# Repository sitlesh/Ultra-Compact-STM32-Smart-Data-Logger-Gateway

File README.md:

# Custom Embedded Controller Board with Micro SD Storage

A professionally designed, compact **2-layer printed circuit board (PCB)** developed using **KiCad 8.0**. This hardware platform is engineered for standalone embedded applications requiring localized data logging, high-precision timing, and robust power delivery.

---

## 📸 Hardware Showcase

### 🏷️ 3D Render Preview

### 🗺️ Board Layout (Top & Bottom View)
| Top Copper Layer (F.Cu) | Bottom Copper Layer (B.Cu) |
| :---: | :---: |
|  |  |

---

## 🚀 Key Hardware Features

* **Micro SD Card Slot (J4):** Wired via high-speed SPI interface. Features localized decoupling, direct short-return paths to ground, and integrated mechanical shield grounding (`SH GND`) to suppress ESD and EMI.
* **Dual-Clock Architecture:** * **High-Speed Crystal (Y1 - 8MHz):** Provides a stable external clock source for the primary microcontroller core, stabilized by 20pF loading capacitors.
  * **Low-Speed RTC Crystal (Y2 - 32.768kHz):** Dedicated ultra-low-power crystal with 10pF loading capacitors for precise time-stamping.
* **Power Management:** Heavy-duty 2-position screw terminal (`J1`) for power input, protected by a robust on-board Schottky/Rectifier Diode (`D1`) for reverse polarity protection.
* **Signal Integrity:** Utilizes duplicated, stitched copper zones (`GND`) across both layers to maximize thermal dissipation, lower loop inductance, and suppress high-frequency noise.

---

## 📁 Repository Directory & File Descriptions

This repository contains all the native design assets and manufacturing files required to replicate or modify this project.

### 🛠️ Source Design Files (KiCad 8.0)
* **[`Ultra-Compact STM32 Smart Data Logger & Gateway.kicad_pro`](./Ultra-Compact%20STM32%20Smart%20Data%20Logger%20%26%20Gateway.kicad_pro)** : The master KiCad project file that links the schematic and PCB layout configurations together.
* **[`Ultra-Compact STM32 Smart Data Logger & Gateway.kicad_sch`](./Ultra-Compact%20STM32%20Smart%20Data%20Logger%20%26%20Gateway.kicad_sch)** : The complete schematic capture. Contains the logical circuit connections, component symbols, and electrical nets.
* **[`Ultra-Compact STM32 Smart Data Logger & Gateway.kicad_pcb`](./Ultra-Compact%20STM32%20Smart%20Data%20Logger%20%26%20Gateway.kicad_pcb)** : The physical 2-layer board layout, trace routing, component footprints, and copper ground planes.
* **[`gitignore.txt`](./gitignore.txt)** : Configured to exclude local KiCad auto-saves and temporary backup files to keep the repository clean.

### 📦 Manufacturing Files
* **[`Download Pre-packaged Gerbers ZIP (Gerbers.zip)`](./Gerbers.zip)** : Contains the combined ZIP archive. Click this link and hit the **Download** button on the next page to get all production-ready Gerber and Drill files for direct manufacturing.

---

## ⚙️ Fabrication Specifications

| Parameter | Specification |
| :--- | :--- |
| **Material Type** | FR-4 Standard |
| **Layer Count** | 2 Layers |
| **Board Thickness** | 1.6 mm |
| **Copper Weight** | 1 oz (35μm) outer layers |
| **Surface Finish** | HASL (with lead) or ENIG |
| **Solder Mask** | User Preference (Green/Blue/Black) |
| **Silkscreen** | White (High contrast) |

---

## 📝 License
This hardware design is open-source. Feel free to clone, modify, and build upon it for your own custom applications.

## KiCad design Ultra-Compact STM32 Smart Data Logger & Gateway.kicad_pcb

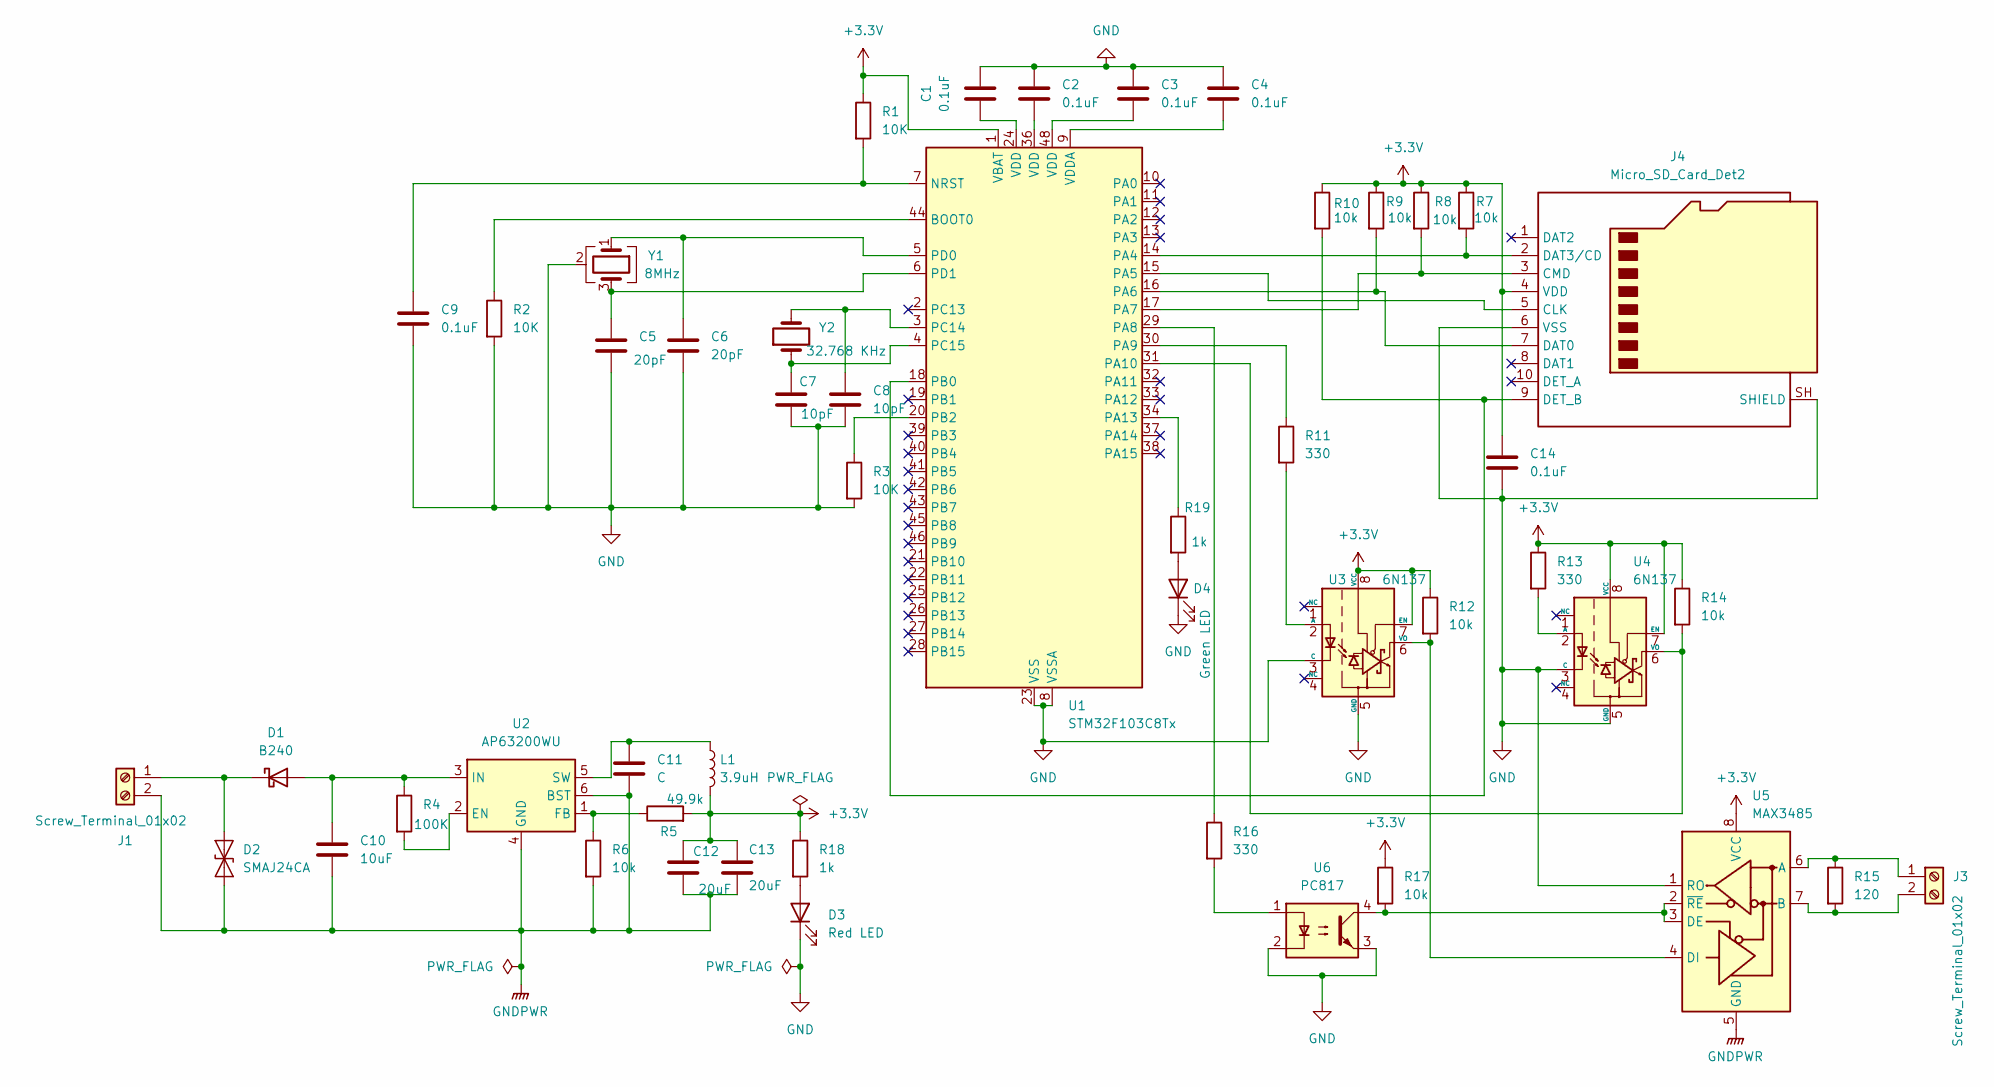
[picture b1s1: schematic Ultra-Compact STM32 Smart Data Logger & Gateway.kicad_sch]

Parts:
C1, C2, C3, C4, C9, C14: 0.1uF; C_0603_1608Metric
C5, C6: 20pF; C_0603_1608Metric
C7, C8: 10pF; C_0603_1608Metric
C10: 10uF; C_0603_1608Metric
C11: C; C_0603_1608Metric
C12, C13: 20uF; C_0603_1608Metric
D1: B240; D_SMB
D2: SMAJ24CA; D_SMA
D3: Red LED; LED_0805_2012Metric
D4: Green LED; LED_0805_2012Metric
J1, J3: Screw_Terminal_01x02; TerminalBlock_Phoenix_MKDS-1,5-2-5.08_1x02_P5.08mm_Horizont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
J4: Micro_SD_Card_Det2; microSD_HC_Molex_104031-0811
L1: 3.9uH; L_6.3x6.3_H3
R1, R2, R3: 10K; R_0805_2012Metric
R4: 100K; R_0805_2012Metric
R5: 49.9k; R_0805_2012Metric
R6, R7, R8, R9, R10, R12, R14, R17: 10k; R_0805_2012Metric
R11, R13, R16: 330; R_0805_2012Metric
R15: 120; R_0805_2012Metric
R18, R19: 1k; R_0805_2012Metric
U1: STM32F103C8Tx; LQFP-48_7x7mm_P0.5mm
U2: AP63200WU; TSOT-23-6
U3, U4: 6N137; SMDIP-8_W7.62mm
U5: MAX3485; SOIC-8_3.9x4.9mm_P1.27mm
U6: PC817; SMDIP-4_W7.62mm
Y1: 8MHz; Crystal_SMD_3225-4Pin_3.2x2.5mm
Y2: 32.768 KHz; Crystal_SMD_2012-2Pin_2.0x1.2mm

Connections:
+3.3V: C12.1, C13.1, C14.1, J4.4 (VDD), L1.2, R1.1, R5.2, R7.1, R8.1, R9.1, R10.1, R12.1, R13.1, R14.1, R17.1, R18.1, U1.1 (VBAT), U3.7 (EN), U3.8 (VCC), U4.7 (EN), U4.8 (VCC), U5.8 (VCC)
GND: C1.2, C2.2, C3.2, C4.2, C5.2, C6.2, C7.2, C8.2, C9.2, C14.2, D3.1 (K), D4.1 (K), J4.6 (VSS), J4.SH (SHIELD), R2.2, R3.2, U1.8 (VSSA), U1.23 (VSS), U1.35 (VSS), U1.47 (VSS), U3.3 (C), U3.5 (GND), U4.3 (C), U4.5 (GND), U5.1 (RO), U6.2, U6.3, Y1.2 (G), Y1.4 (G)
GNDPWR: C10.2, C11.2, C12.2, C13.2, D2.1 (A1), J1.2, R6.2, U2.4 (GND), U2.6 (BST), U5.5 (GND)
unnamed: C1.1, U1.24 (VDD)
unnamed: C2.1, U1.36 (VDD)
unnamed: C3.1, U1.48 (VDD)
unnamed: C10.1, D1.2 (A), R4.1, U2.3 (IN)
unnamed: D1.1 (K), D2.2 (A2), J1.1
unnamed: D3.2 (A), R18.2
unnamed: D4.2 (A), R19.2
unnamed: J3.1, R15.1, U5.6 (A)
unnamed: J3.2, R15.2, U5.7 (B)
unnamed: J4.5 (CLK), U1.15 (PA5)
unnamed: J4.3 (CMD), R8.2, U1.17 (PA7)
unnamed: J4.7 (DAT0), R9.2, U1.16 (PA6)
unnamed: J4.2 (DAT3/CD), R7.2, U1.14 (PA4)
unnamed: J4.9 (DET_B), R10.2, U1.18 (PB0)
unnamed: R16.2, U6.1
unnamed: R2.1, U1.44 (BOOT0)
unnamed: C9.1, R1.2, U1.7 (NRST)
unnamed: R16.1, U1.29 (PA8)
unnamed: R11.1, U1.30 (PA9)
unnamed: R14.2, U1.31 (PA10), U4.6 (VO)
unnamed: R19.1, U1.34 (PA13)
unnamed: R3.1, U1.20 (PB2)
unnamed: C8.1, U1.3 (PC14), Y2.2
unnamed: C7.1, U1.4 (PC15), Y2.1
unnamed: C6.1, U1.5 (PD0), Y1.1
unnamed: C5.1, U1.6 (PD1), Y1.3
unnamed: C4.1, U1.9 (VDDA)
unnamed: R4.2, U2.2 (EN)
unnamed: R5.1, R6.1, U2.1 (FB)
unnamed: C11.1, L1.1, U2.5 (SW)
unnamed: R11.2, U3.2 (A)
unnamed: R12.2, U3.6 (VO), U5.4 (DI)
unnamed: R13.2, U4.2 (A)
unnamed: R17.2, U5.2 (~RE), U5.3 (DE), U6.4

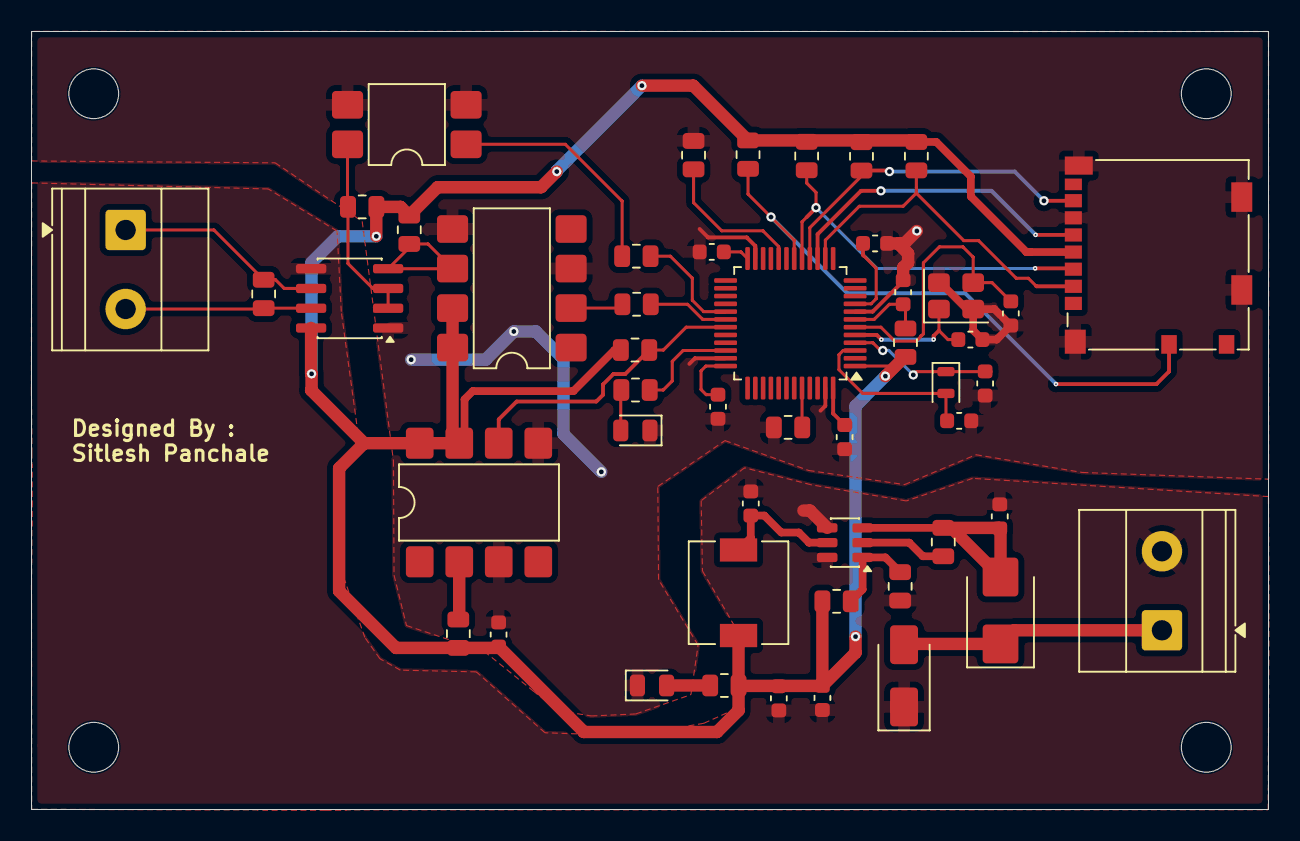
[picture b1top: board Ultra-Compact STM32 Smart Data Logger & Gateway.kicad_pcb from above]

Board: 2 copper layers, 79.5 x 50.0 mm, 49 parts (0 on the bottom side), 37 nets.

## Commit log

2026-05-26 Rename .gitignore.txt to .gitignore
